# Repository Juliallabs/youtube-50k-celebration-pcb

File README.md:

## ⭐ Youtube 50k celebration PCB

Este projeto é uma placa de circuito impresso desenvolvida usando o [Eagle](https://www.autodesk.com/products/eagle/overview) como comemoração aos 50 mil inscritos no [meu canal no youtube](https://www.youtube.com/@LaboratoriodaJulia).

## 📝 Esquemático

## ⚙️ Componentes necessários para o projeto (BOM LIST)
kd bom list

## 🤝 Parcerias
Este projeto foi desenvolvido em parceria com:

## 📹 Vídeos relacionados
Veja alguns vídeos que produzi relacionados a este projeto:
- [FIZ MINHA PRÓRIA PLACA DE 50K DO YOUTUBE!](https://www.youtube.com/watch?v=WPf2E2vhGY4)
- [PCB DESIGN - Como faço meus projetos](https://www.youtube.com/watch?v=2eLVXtOEY-U)
- [MINHA COLEÇÃO DE PLACAS DE CIRCUITO IMPRESSO](https://www.youtube.com/watch?v=9CJyRkSh-_w)

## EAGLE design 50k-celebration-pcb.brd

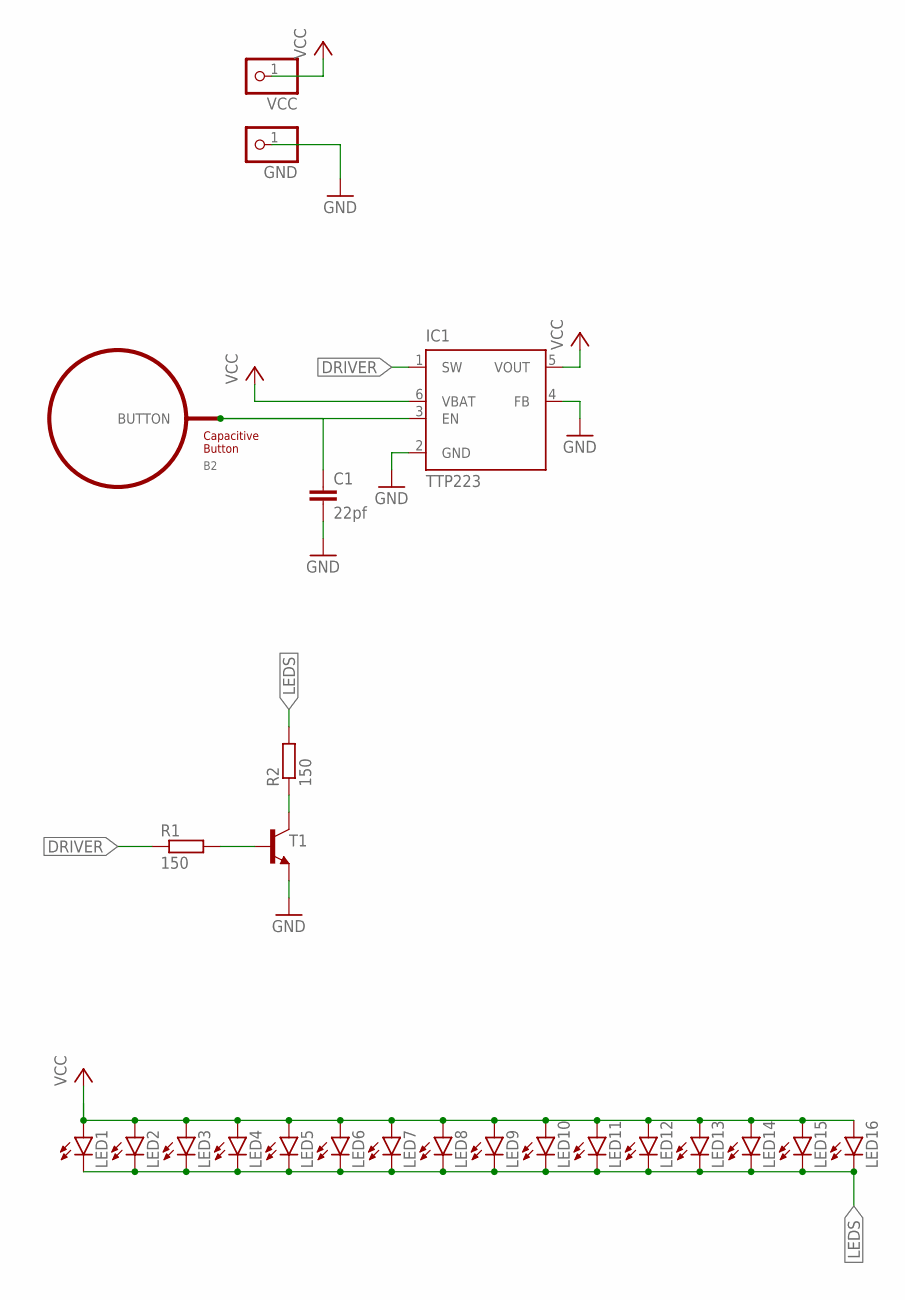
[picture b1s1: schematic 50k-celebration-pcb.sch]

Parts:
B2: BUTTON_PASSIVE8MM; BUTTON_PASSIVE_8MM
C1: 22pf; C0805
GND: WPAD-1-SQ-0.5MM
IC1: TTP223; TSOT23-6_DDC
LED1, LED2, LED3, LED4, LED5, LED6, LED7, LED8, LED9, LED10, LED11, LED12, LED13, LED14, LED15, LED16: LEDCHIP-LED0805; CHIP-LED0805
R1, R2: 150; M0805
T1: BC817-16LT1-NPN-SOT23-BEC; SOT23-BEC
VCC: WPAD-1-SQ-0.5MM

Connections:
DRIVER: IC1.1 (SW), R1.1
GND: C1.2, GND.1, IC1.2 (GND), IC1.4 (FB), T1.E
LEDS: LED1.C, LED2.C, LED3.C, LED4.C, LED5.C, LED6.C, LED7.C, LED8.C, LED9.C, LED10.C, LED11.C, LED12.C, LED13.C, LED14.C, LED15.C, LED16.C, R2.2
unnamed: R1.2, T1.B
unnamed: R2.1, T1.C
unnamed: B2.BUTTON, C1.1, IC1.3 (EN)
VCC: IC1.5 (VOUT), IC1.6 (VBAT), LED1.A, LED2.A, LED3.A, LED4.A, LED5.A, LED6.A, LED7.A, LED8.A, LED9.A, LED10.A, LED11.A, LED12.A, LED13.A, LED14.A, LED15.A, LED16.A, VCC.1

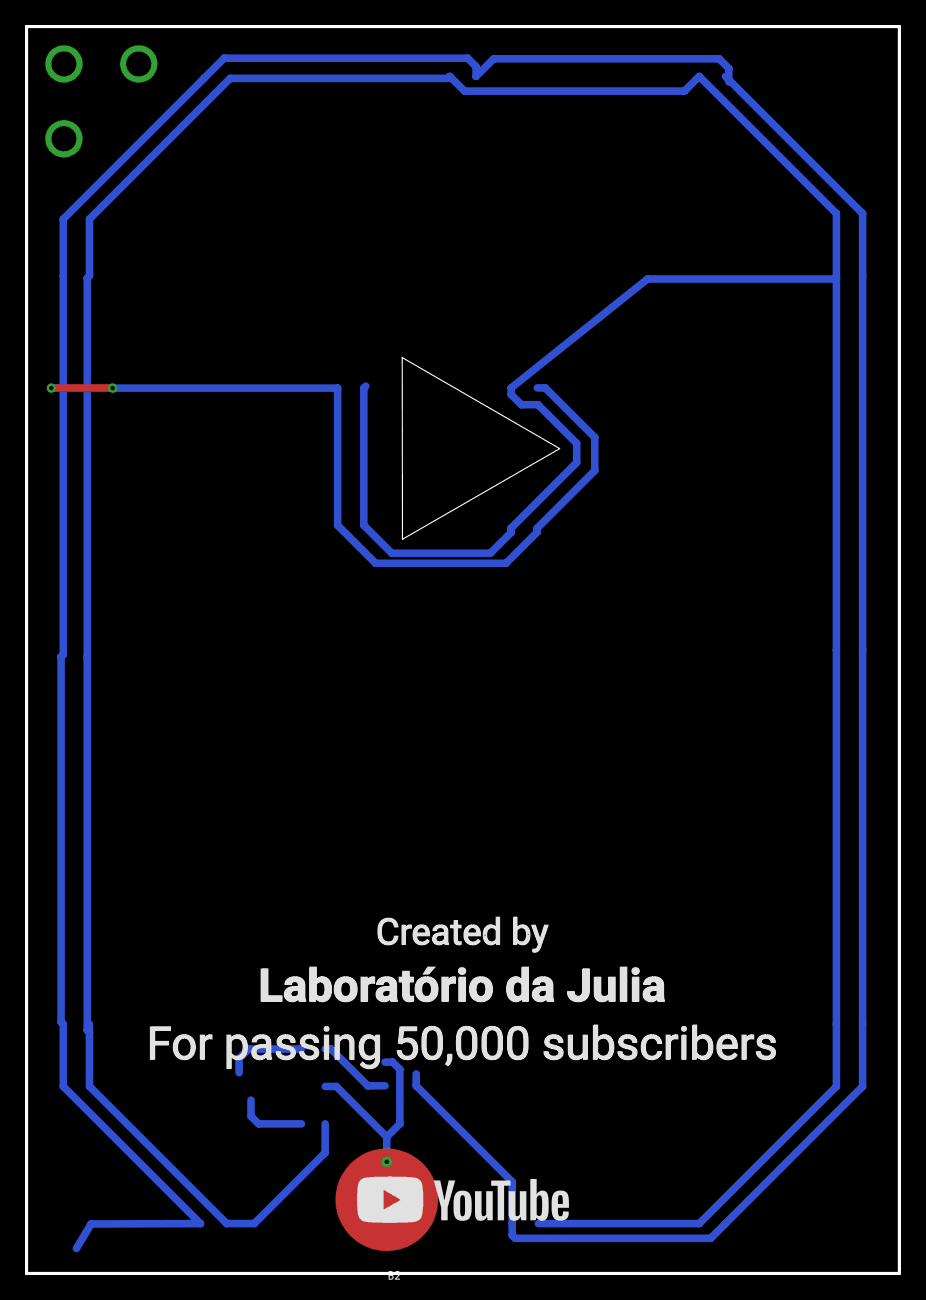
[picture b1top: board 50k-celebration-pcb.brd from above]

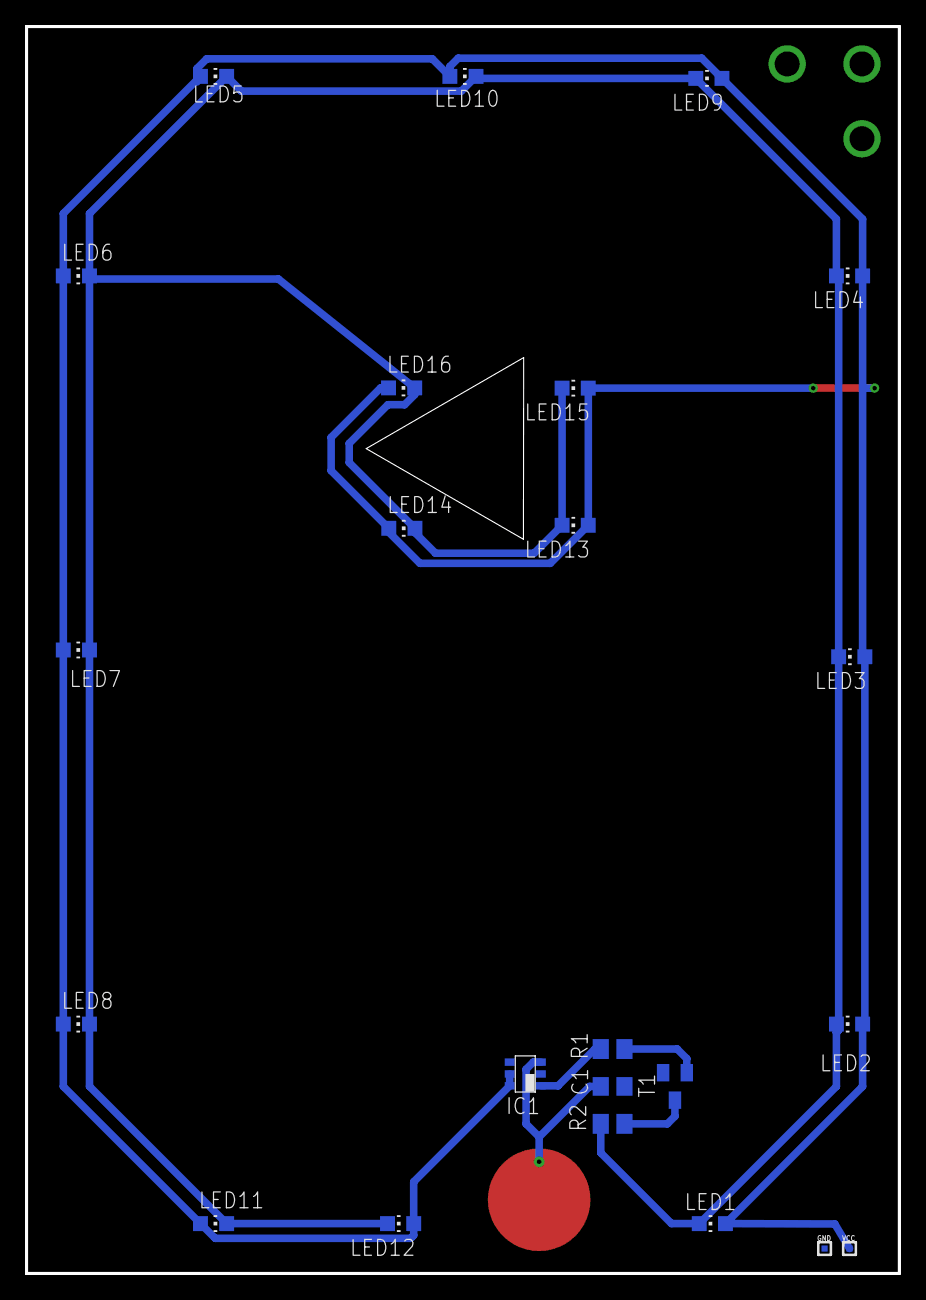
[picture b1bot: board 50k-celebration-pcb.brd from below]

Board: 2 copper layers, 70.0 x 100.0 mm, 24 parts (23 on the bottom side), 7 nets.

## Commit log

2023-07-08 Organização e primeiro rascunho do README

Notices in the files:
parts and their libraries:
PatternAgents-TouchWidgets: License : http://creativecommons.org/licenses/by-sa/4.0/ (Creative Commons 4.0)
PatternAgents-TouchWidgets: License : http://creativecommons.org/licenses/by-sa/3.1/ (Creative Commons 3.1)
PatternAgents-ProtoPads: License : http://creativecommons.org/licenses/by-sa/4.0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
